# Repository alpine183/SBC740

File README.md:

# SBC740
Mitsbishi MELPS750 (M50747) SBC

See https://almostlosttechnology.hatenablog.com/archive/category/MELPS740

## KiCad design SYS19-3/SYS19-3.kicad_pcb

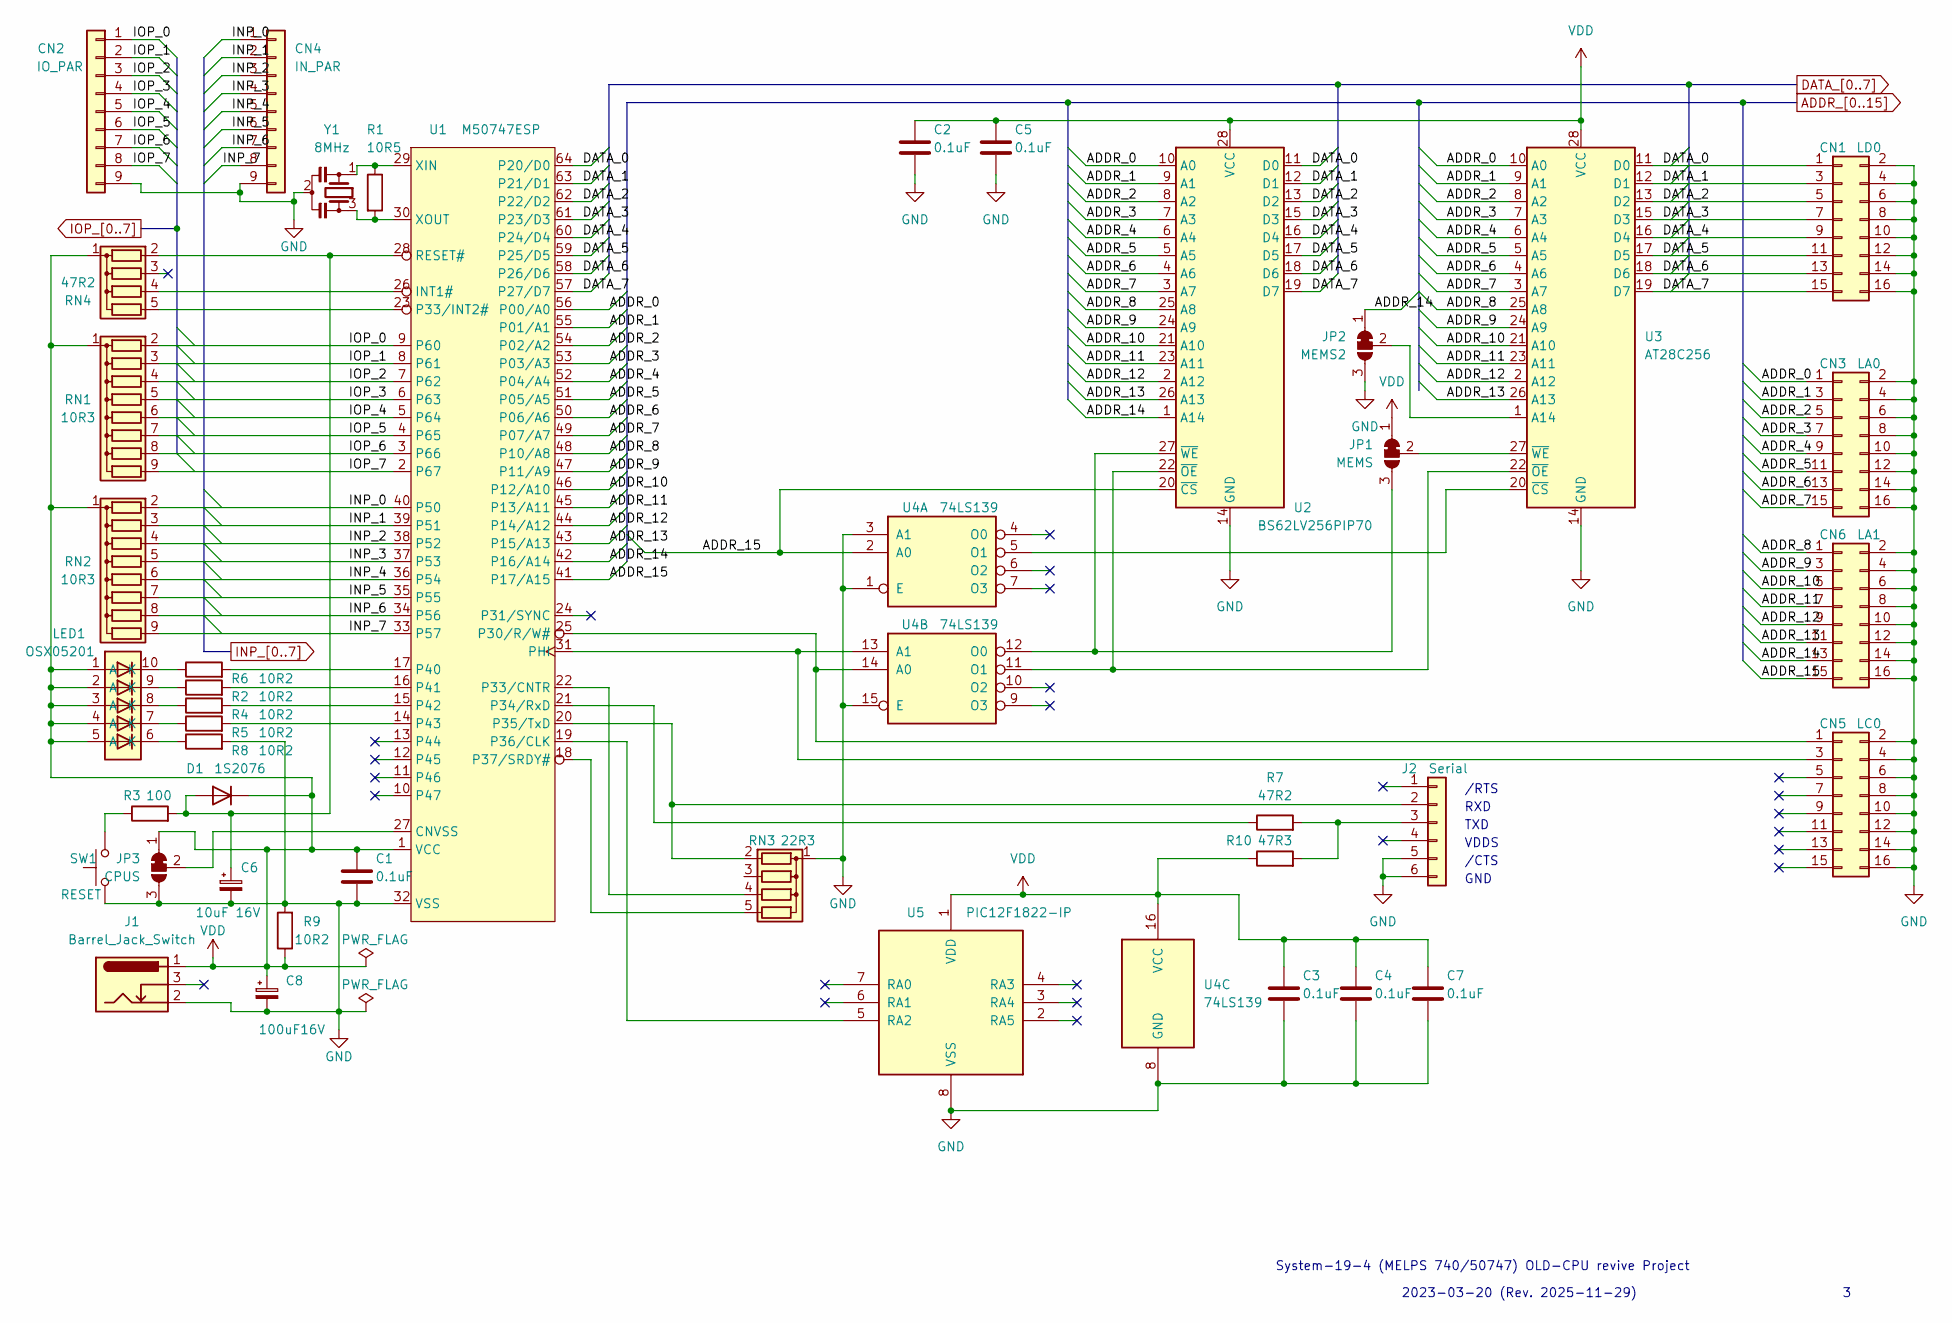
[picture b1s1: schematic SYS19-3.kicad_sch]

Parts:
C1, C2, C3, C4, C5, C7: 0.1uF; C_Disc_D3.0mm_W2.0mm_P2.50mm
C6: 10uF 16V; CP_Radial_D4.0mm_P2.00mm
C8: 100uF16V; CP_Radial_D6.3mm_P2.50mm
CN1: LD0; PinHeader_2x08_P2.54mm_Vertical
CN2: IO_PAR; Molex_SL_171971-0009_1x09_P2.54mm_Vertical
CN3: LA0; PinHeader_2x08_P2.54mm_Vertical
CN4: IN_PAR; Molex_SL_171971-0009_1x09_P2.54mm_Vertical
CN5: LC0; PinHeader_2x08_P2.54mm_Vertical
CN6: LA1; PinHeader_2x08_P2.54mm_Vertical
D1: 1S2076; D_DO-35_SOD27_P7.62mm_Horizontal
J1: Barrel_Jack_Switch; BarrelJack_Kycon_KLDX-0202-xC_Horizontal
J2: Serial; Molex_SL_171971-0006_1x06_P2.54mm_Vertical
JP1: MEMS; SolderJumper-3_P1.3mm_Bridged12_RoundedPad1.0x1.5mm
JP2: MEMS2; SolderJumper-3_P1.3mm_Bridged12_RoundedPad1.0x1.5mm
JP3: CPUS; SolderJumper-3_P1.3mm_Bridged12_RoundedPad1.0x1.5mm
LED1: OSX05201; DIP-10_W7.62mm-WIDE
R1: 10R5; R_Axial_DIN0204_L3.6mm_D1.6mm_P7.62mm_Horizontal
R2, R4, R5, R6, R8, R9: 10R2; R_Axial_DIN0204_L3.6mm_D1.6mm_P7.62mm_Horizontal
R3: 100; R_Axial_DIN0204_L3.6mm_D1.6mm_P7.62mm_Horizontal
R7: 47R2; R_Axial_DIN0204_L3.6mm_D1.6mm_P7.62mm_Horizontal
R10: 47R3; R_Axial_DIN0204_L3.6mm_D1.6mm_P7.62mm_Horizontal
RN1, RN2: 10R3; R_Array_SIP9
RN3: 22R3; R_Array_SIP5
RN4: 47R2; R_Array_SIP5
SW1: RESET; SW_PUSH_6mm
U1: M50747ESP; SDIP64-750mil
U2: BS62LV256PIP70; DIP-28_W15.24mm
U3: AT28C256; DIP-28_W15.24mm
U4: 74LS139; DIP-16_W7.62mm
U5: PIC12F1822-IP; DIP-8_W7.62mm
Y1: 8MHz; Resonator-3Pin_W7.0mm_H2.5mm

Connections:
ADDR_0: CN3.1, U1.56 (P00/A0), U2.10 (A0), U3.10 (A0)
ADDR_1: CN3.3, U1.55 (P01/A1), U2.9 (A1), U3.9 (A1)
ADDR_2: CN3.5, U1.54 (P02/A2), U2.8 (A2), U3.8 (A2)
ADDR_3: CN3.7, U1.53 (P03/A3), U2.7 (A3), U3.7 (A3)
ADDR_4: CN3.9, U1.52 (P04/A4), U2.6 (A4), U3.6 (A4)
ADDR_5: CN3.11, U1.51 (P05/A5), U2.5 (A5), U3.5 (A5)
ADDR_6: CN3.13, U1.50 (P06/A6), U2.4 (A6), U3.4 (A6)
ADDR_7: CN3.15, U1.49 (P07/A7), U2.3 (A7), U3.3 (A7)
ADDR_8: CN6.1, U1.48 (P10/A8), U2.25 (A8), U3.25 (A8)
ADDR_9: CN6.3, U1.47 (P11/A9), U2.24 (A9), U3.24 (A9)
ADDR_10: CN6.5, U1.46 (P12/A10), U2.21 (A10), U3.21 (A10)
ADDR_11: CN6.7, U1.45 (P13/A11), U2.23 (A11), U3.23 (A11)
ADDR_12: CN6.9, U1.44 (P14/A12), U2.2 (A12), U3.2 (A12)
ADDR_13: CN6.11, U1.43 (P15/A13), U2.26 (A13), U3.26 (A13)
ADDR_14: CN6.13, JP2.1 (A), U1.42 (P16/A14), U2.1 (A14)
ADDR_15: CN6.15, U1.41 (P17/A15), U2.20 (~CS), U4.2 (A0)
DATA_0: CN1.1, U1.64 (P20/D0), U2.11 (D0), U3.11 (D0)
DATA_1: CN1.3, U1.63 (P21/D1), U2.12 (D1), U3.12 (D1)
DATA_2: CN1.5, U1.62 (P22/D2), U2.13 (D2), U3.13 (D2)
DATA_3: CN1.7, U1.61 (P23/D3), U2.15 (D3), U3.15 (D3)
DATA_4: CN1.9, U1.60 (P24/D4), U2.16 (D4), U3.16 (D4)
DATA_5: CN1.11, U1.59 (P25/D5), U2.17 (D5), U3.17 (D5)
DATA_6: CN1.13, U1.58 (P26/D6), U2.18 (D6), U3.18 (D6)
DATA_7: CN1.15, U1.57 (P27/D7), U2.19 (D7), U3.19 (D7)
GND: C1.2, C2.2, C3.2, C4.2, C5.2, C6.2, C7.2, C8.2, CN1.2, CN1.4, CN1.6, CN1.8, CN1.10, CN1.12, CN1.14, CN1.16, CN2.9, CN3.2, CN3.4, CN3.6, CN3.8, CN3.10, CN3.12, CN3.14, CN3.16, CN4.9, CN5.2, CN5.4, CN5.6, CN5.8, CN5.10, CN5.12, CN5.14, CN5.16, CN6.2, CN6.4, CN6.6, CN6.8, CN6.10, CN6.12, CN6.14, CN6.16, J1.2, J2.5, J2.6, JP2.3 (B), JP3.3 (B), R8.2, R9.2, RN3.1 (common), SW1.1, U1.32 (VSS), U2.14 (GND), U3.14 (GND), U4.1 (E), U4.3 (A1), U4.8 (GND), U4.15 (E), U5.8 (VSS), Y1.2; also elsewhere on the board
INP_0: CN4.1, RN2.2 (R1), U1.40 (P50)
INP_1: CN4.2, RN2.3 (R2), U1.39 (P51)
INP_2: CN4.3, RN2.4 (R3), U1.38 (P52)
INP_3: CN4.4, RN2.5 (R4), U1.37 (P53)
INP_4: CN4.5, RN2.6 (R5), U1.36 (P54)
INP_5: CN4.6, RN2.7 (R6), U1.35 (P55)
INP_6: CN4.7, RN2.8 (R7), U1.34 (P56)
INP_7: CN4.8, RN2.9 (R8), U1.33 (P57)
IOP_0: CN2.1, RN1.2 (R1), U1.9 (P60)
IOP_1: CN2.2, RN1.3 (R2), U1.8 (P61)
IOP_2: CN2.3, RN1.4 (R3), U1.7 (P62)
IOP_3: CN2.4, RN1.5 (R4), U1.6 (P63)
IOP_4: CN2.5, RN1.6 (R5), U1.5 (P64)
IOP_5: CN2.6, RN1.7 (R6), U1.4 (P65)
IOP_6: CN2.7, RN1.8 (R7), U1.3 (P66)
IOP_7: CN2.8, RN1.9 (R8), U1.2 (P67)
unnamed: CN5.1, U1.25 (P30/R/W#), U4.14 (A0)
unnamed: CN5.3, U1.31 (PHI), U4.13 (A1)
unnamed: C6.1, D1.2 (A), R3.2, RN4.2 (R1), U1.28 (RESET#)
unnamed: J2.2, RN3.2 (R1), U1.20 (P35/TxD)
unnamed: J2.3, R7.2, R10.2
unnamed: JP1.3 (B), U2.27 (~WE), U4.12 (O0)
unnamed: JP1.2 (C), U3.27 (~WE)
unnamed: JP2.2 (C), U3.1 (A14)
unnamed: JP3.2 (C), U1.27 (CNVSS)
unnamed: LED1.6 (K), R8.1
unnamed: LED1.7 (K), R5.1
unnamed: LED1.8 (K), R4.1
unnamed: LED1.9 (K), R2.1
unnamed: LED1.10 (K), R6.1
unnamed: R3.1, SW1.2
unnamed: RN3.4 (R3), U1.22 (P33/CNTR)
unnamed: RN3.5 (R4), U1.18 (P37/SRDY#)
unnamed: RN4.4 (R3), U1.26 (INT1#)
unnamed: RN4.5 (R4), U1.23 (P33/INT2#)
unnamed: R7.1, U1.21 (P34/RxD)
unnamed: U1.19 (P36/CLK), U5.5 (RA2)
unnamed: R6.2, U1.17 (P40)
unnamed: R2.2, U1.16 (P41)
unnamed: R4.2, U1.15 (P42)
unnamed: R5.2, U1.14 (P43)
unnamed 66: R1.1, U1.29 (XIN), Y1.1; also elsewhere on the board
unnamed 67: R1.2, U1.30 (XOUT), Y1.3; also elsewhere on the board
unnamed: U2.22 (~OE), U3.22 (~OE), U4.11 (O1)
unnamed: U3.20 (~CS), U4.5 (O1)
VDD: C1.1, C2.1, C3.1, C4.1, C5.1, C7.1, C8.1, D1.1 (K), J1.1, JP1.1 (A), JP3.1 (A), LED1.1 (A), LED1.2 (A), LED1.3 (A), LED1.4 (A), LED1.5 (A), R9.1, R10.1, RN1.1 (common), RN2.1 (common), RN4.1 (common), U1.1 (VCC), U2.28 (VCC), U3.28 (VCC), U4.16 (VCC), U5.1 (VDD)

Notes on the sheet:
VDDS
2023-03-20 (Rev. 2025-11-29)
GND
/RTS
TXD
System-19-4 (MELPS 740/50747) OLD-CPU revive Project
RXD
/CTS

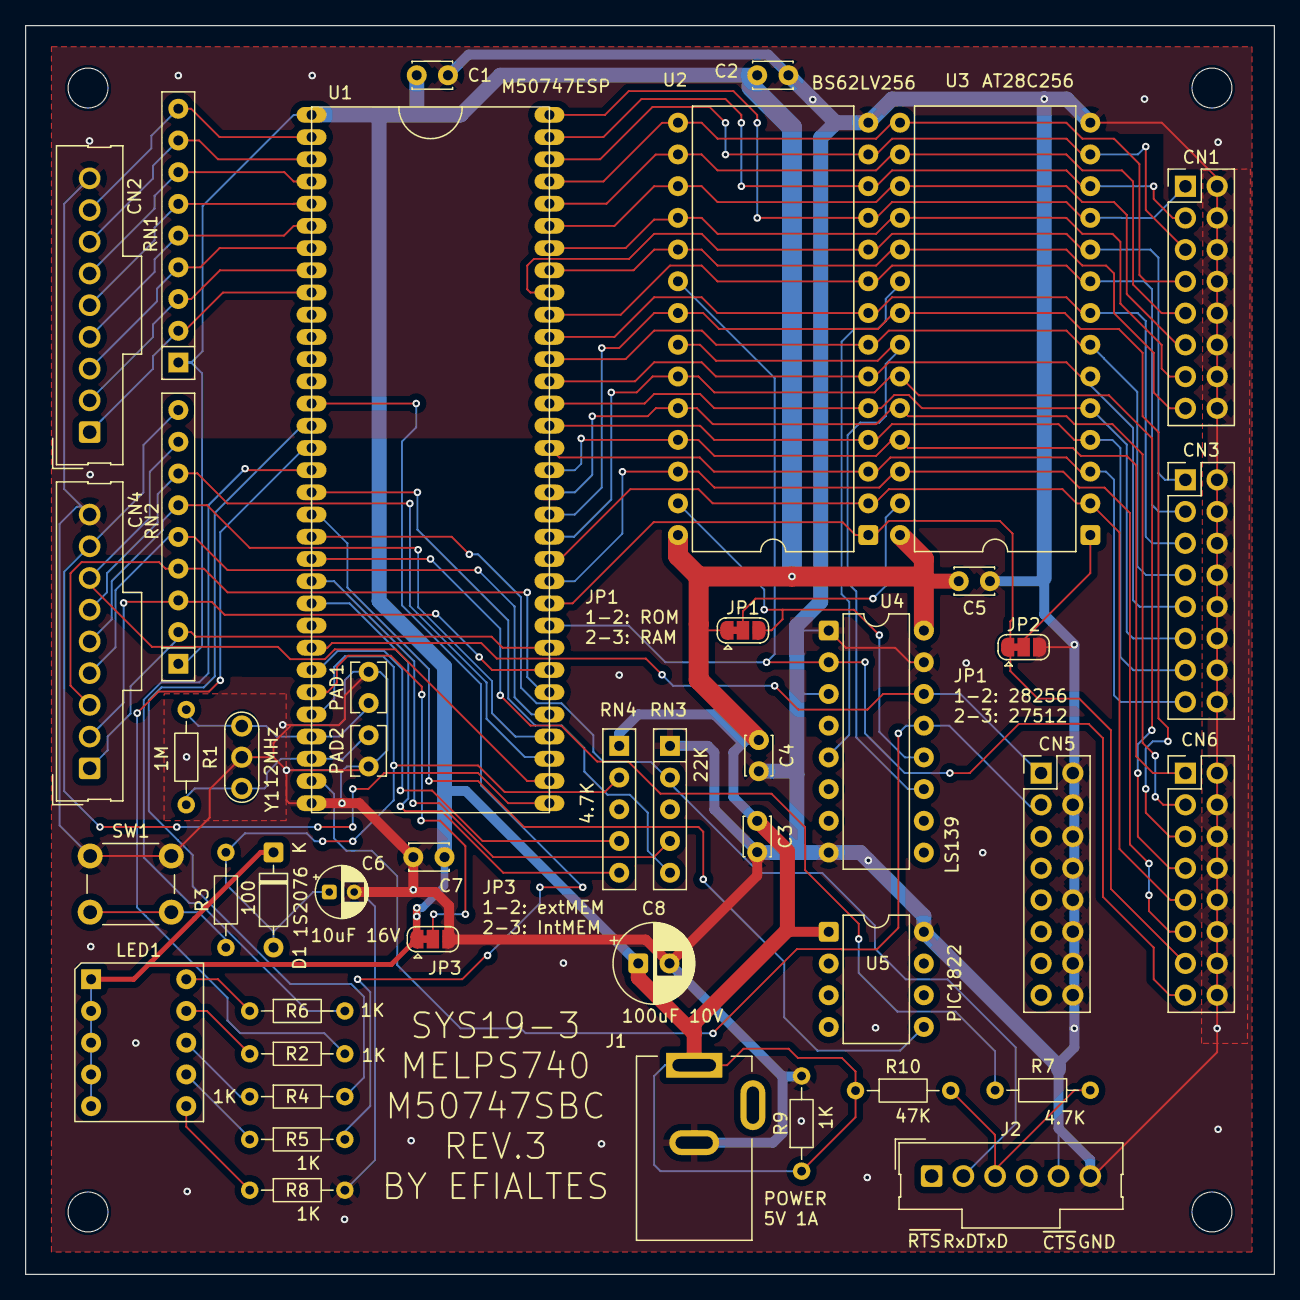
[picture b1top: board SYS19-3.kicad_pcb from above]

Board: 2 copper layers, 100.0 x 100.0 mm, 48 parts (0 on the bottom side), 71 nets.

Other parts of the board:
MH1, MH2, MH3, MH4: MountingHole_3.2mm_M3
PAD1, PAD2: C_Disc_D3.8mm_W2.6mm_P2.50mm

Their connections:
GND: PAD1.2, PAD2.1; also elsewhere on the board
unnamed 66: PAD1.1; also elsewhere on the board
unnamed 67: PAD2.2; also elsewhere on the board

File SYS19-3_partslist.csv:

"Reference","Value","Datasheet","Footprint","Qty","DNP"
"C1,C2,C3,C4,C5,C7","0.1uF","~","Capacitor_THT:C_Disc_D3.0mm_W2.0mm_P2.50mm","6",""
"C6","10uF 16V","~","Capacitor_THT:CP_Radial_D4.0mm_P2.00mm","1",""
"C8","100uF16V","~","Capacitor_THT:CP_Radial_D6.3mm_P2.50mm","1",""
"CN1","LD0","~","Connector_PinHeader_2.54mm:PinHeader_2x08_P2.54mm_Vertical","1",""
"CN2","IO_PAR","~","Connector_Molex:Molex_SL_171971-0009_1x09_P2.54mm_Vertical","1",""
"CN3","LA0","~","Connector_PinHeader_2.54mm:PinHeader_2x08_P2.54mm_Vertical","1",""
"CN4","IN_PAR","~","Connector_Molex:Molex_SL_171971-0009_1x09_P2.54mm_Vertical","1",""
"CN5","LC0","~","Connector_PinHeader_2.54mm:PinHeader_2x08_P2.54mm_Vertical","1",""
"CN6","LA1","~","Connector_PinHeader_2.54mm:PinHeader_2x08_P2.54mm_Vertical","1",""
"D1","1S2076","https://assets.nexperia.com/documents/data-sheet/1N4148_1N4448.pdf","Diode_THT:D_DO-35_SOD27_P7.62mm_Horizontal","1",""
"J1","Barrel_Jack_Switch","~","Connector_BarrelJack:BarrelJack_Kycon_KLDX-0202-xC_Horizontal","1",""
"J2","Serial","~","Connector_Molex:Molex_SL_171971-0006_1x06_P2.54mm_Vertical","1",""
"JP1","MEMS","~","Jumper:SolderJumper-3_P1.3mm_Bridged12_RoundedPad1.0x1.5mm","1",""
"JP2","MEMS2","~","Jumper:SolderJumper-3_P1.3mm_Bridged12_RoundedPad1.0x1.5mm","1",""
"JP3","CPUS","~","Jumper:SolderJumper-3_P1.3mm_Bridged12_RoundedPad1.0x1.5mm","1",""
"LED1","OSX05201","","0-OLDCPU-ELSE:DIP-10_W7.62mm-WIDE","1",""
"R1","10R5","~","Resistor_THT:R_Axial_DIN0204_L3.6mm_D1.6mm_P7.62mm_Horizontal","1",""
"R2,R4,R5,R6,R8,R9","10R2","~","Resistor_THT:R_Axial_DIN0204_L3.6mm_D1.6mm_P7.62mm_Horizontal","6",""
"R3","100","~","Resistor_THT:R_Axial_DIN0204_L3.6mm_D1.6mm_P7.62mm_Horizontal","1",""
"R7,RN4","47R2","http://www.vishay.com/docs/31509/csc.pdf,~","Resistor_THT:R_Array_SIP5,Resistor_THT:R_Axial_DIN0204_L3.6mm_D1.6mm_P7.62mm_Horizontal","2",""
"R10","47R3","~","Resistor_THT:R_Axial_DIN0204_L3.6mm_D1.6mm_P7.62mm_Horizontal","1",""
"RN1,RN2","10R3","http://www.vishay.com/docs/31509/csc.pdf","Resistor_THT:R_Array_SIP9","2",""
"RN3","22R3","http://www.vishay.com/docs/31509/csc.pdf","Resistor_THT:R_Array_SIP5","1",""
"SW1","RESET","~","Button_Switch_THT:SW_PUSH_6mm","1",""
"U1","M50747ESP","","0-OLDCPU-ELSE:SDIP64-750mil","1",""
"U2","BS62LV256PIP70","http://ww1.microchip.com/downloads/en/DeviceDoc/doc0006.pdf","Package_DIP:DIP-28_W15.24mm","1",""
"U3","AT28C256","http://ww1.microchip.com/downloads/en/DeviceDoc/doc0006.pdf","Package_DIP:DIP-28_W15.24mm","1",""
"U4","74LS139","http://www.ti.com/lit/ds/symlink/sn74ls139a.pdf","Package_DIP:DIP-16_W7.62mm","1",""
"U5","PIC12F1822-IP","http://ww1.microchip.com/downloads/en/DeviceDoc/41413B.pdf","Package_DIP:DIP-8_W7.62mm","1",""
"Y1","8MHz","~","Crystal:Resonator-3Pin_W7.0mm_H2.5mm","1",""

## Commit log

2026-03-02 add links.
